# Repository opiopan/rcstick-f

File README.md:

rcstick-f
====

rcstick-f is a USB HID device which has 8 analog axis.
And this device is also a RF receiver which conplient with Futaba S-FHSS protocol.<br>
This device is designed to be used to controll RC flight simulator by Futaba RC transmitter.

One of the most simple and common way to use RC transmitter as controller of RC flight simulator is handling PPM signal exported from the trainer port on a transmitter.<br>
Some simulator software can recognize PPM signal through audio input, So in this case, you have to do is just connect cable between the trainer port on a transmitter and mic input port on a PC.<br>
Or using USB dongle that convert PPM signal to USB HID device, such as [these products](https://www.ebay.com/sch/i.html?_nkw=RC+simulator+USB+dongle+cable&_sacat=0&LH_TitleDesc=0&_osacat=0&_odkw=rc+simulator+usb+dongle), is also popular.<br>
The advantages of these PPM signal based solution are inexpencive and compatibe with many transmitter products. The most disadvantages is that the cable between  a transmitter and PC is very annoying.

On the other hand, in recent years, the products that behave wireless RF receiver and USB HID device have appeared in the world. For example, [SPEKTRUM WS1000](https://www.spektrumrc.com/Products/Default.aspx?ProdID=SPMWS1000) for DSM2/DSMX protocol or [FrSky XSR-SIM](https://www.frsky-rc.com/product/xsr-sim/) for FrSky protocol.<br>
These products are designed for a specific protocol. So comatibility is lower than the PPM signal based solution. However, users can enjoy highly convenience due to wireless connection.<br>
In addition, that is more responsive and higher precision than the PPM signale based solution since there is no unnecessary data conversion such as ADC data to PPM.

The reason why I determined to start this project is that I could'nt find a such kind of wireless device supported Futaba RC protocol. (As of the begging of 2019)<br>

## Futaba S-FHSS protocol
S-FHSS is a 2.4 GHz band based RC transceiver protocol designed by Futaba.
It is not brand new protocol, However many Futaba transmitter suport this protolol. And this protocol is well analyzed. That's why I choose S-FHSS for my own receiver imprementation.

[This commentary article](https://rfengfpv.wordpress.com/2017/01/10/futaba-s-fhss-protocol-overview/) and
[this C source code](https://github.com/DeviationTX/deviation/blob/2ce0f46fe94d80198ae94fd5a6f6a008863ec420/src/protocol/sfhss_cc2500.c)
which impremens S-FHSS transmitter are very helpful to understand the protocol.
I sincerely appreciate there effort.

## PCB Design
I designed two types of PCB artworks for rcstick-f.<br>
One is sufficiently small that QFP32 package of STM32 MCU is installed, the other one is very small that QFN32 package of MCU is installed.

Both artworks are optimized to enable hand soldering by using a soldering iron. You don't need a reflow oven or a hot air gun.<br>
All pads and parts spaceing are designed to allow contacting soldering iron. grand pad located center of QFN package is also able to be soldered through a via from back side of PCB.

January 29th, 2023: USB Type-C connector version was added. |
:-|
The design of USB Type-C version was completed in February 2022, but the production was put on hold because the Type-C plug could not be obtained due to the chip shortage from time to time.<br>Recently, the availability of this part has improved, so I was finally able to manufacture it.<br>This version is also capable of hand soldering, but this time I saved time and effort by using PCB assembly service.

March 18th, 2023: QFN28 MCU version was added. |
:-|
The situation of chip shortage has eased, and the market inventory of STM32 MCUs seems to have increased.<br>However, they seem to be carefully selecting the SKUs they produce, and I received a message from someone that STM32F042K6U* QFN32 package is not available at all.<br>So I made an artwork with STM32F042G6U* QFN28 package which is good availability.<br>Unlike the other three artworks, this is not suitable for hand soldering. Because this MCU is a QFN package that does not have a pad in the center, so it is difficult to implement with a soldering iron. I manufactured it using [JLCPCB's PCB assembly service](https://jlcpcb.com).

### Design FIles
Board Type        | Eagle design files | Gerber files |Files for [JLCPCB PCB assembly service](https://jlcpcb.com/)
------------------|:-:|:-:|:-:
QFP32 MCU version | [pcb/small](pcb/small)| [rcstick-f-gerber.zip](https://raw.githubusercontent.com/wiki/opiopan/rcstick-f/data/rcstick-f-gerber.zip)| -
QFN32 MCU version | [pcb/tiny](pcb/tiny)| [rcstick-f-tiny-gerber.zip](https://raw.githubusercontent.com/wiki/opiopan/rcstick-f/data/rcstick-f-tiny-gerber.zip)| -
QFN32 MCU and USB Type-C version|[pcb/pico](pcb/pico)|[rcstick-f-pico-gerber.zip](https://raw.githubusercontent.com/wiki/opiopan/rcstick-f/data/rcstick-f-pico-gerber.zip)|[rcstick-f-pico-pcba.zip](https://raw.githubusercontent.com/wiki/opiopan/rcstick-f/data/rcstick-f-pico-pcba.zip)
QFN28 MCU and USB Type-C version|[pcb/pico2](pcb/pico2)|[rcstick-f-pico2-gerber.zip](https://raw.githubusercontent.com/wiki/opiopan/rcstick-f/data/rcstick-f-pico2-gerber.zip)|[rcstick-f-pico2-pcba.zip](https://raw.githubusercontent.com/wiki/opiopan/rcstick-f/data/rcstick-f-pico2-pcba.zip)

***Note:***<br>
Thickness of a PCB of the USB Type-c version should be 0.8mm. This constraint depends on the implementation conditions of the Type-C plug [Molex 1054440001](https://www.molex.com/molex/products/part-detail/io_connectors/1054440001).<br>

### Schematic Diagram

### BOM List

Components | Value / Product Number | Remarks
-----------|------------------------|------------------------------
U1         | STM32F042K6T*, STM32F042K6U* or STM32F042G6U* |
U2         | TI CC2500              | 
U3         | MCP1703AT-3302E/CB     | SOT-23 LDO
J1         | MOLEX 48037-0001 or MOLEX 1054440001| USB Type-A or Type-C plug
J2         | MOLEX 53047-0410       | **OPTIONAL for debugging**<br>Firmware downloading can be proceeded by using DFU mode
X1         | 16MHz Crystal (3225)   | load capacitance: 10pF
X2         | 26MHz Crystal (3225)   | load capacitance: 9pF
LED1       | OSBL1608C1A            |
SW1        | ALPS SKRPACE010        |
C1, C2, C9 | 1uF (1005)             |
C3, C4, C10, C11, C12, C15, C16| 0.1uF (1005)           |
C5         | 4.7uF (1005)           |
C6, C7     | 15pF (1005)            | need to change value if X1's load capacitance is not 10pF
C8         | 10nF (1005)
C13, C14, C17| 220pF (1005)
C18, C19   | 12pF (1005)            | need to change value if X2's load capacitance is not 9pF
C20, C21   | 100pF (1005)           |
C22, C23   | 1pF (1005)             |
C24        | 1.8pF (1005)           |
C25        | 1.5pF (1005)           |
R1         | 10K ohm (1005)         | 
R2         | 56K ohm (1005)         |
R3         | 100 ohm (1005)         |
R4         | 5.1K ohm (1005)        | need for only USB Type-C version
L1,L2,L3   | 1.2nH (1005)           |

### Case Design
You can download [STL data](https://raw.githubusercontent.com/wiki/opiopan/rcstick-f/data/case.zip) of case for tiny version of PCB. That is desined assuming that is printed by resin printer.<br>
Note that PCB thickness should be 1.2mm if you apply this case design.

## Building Firmware
1. **Requirements**<br>
[GNU Arm Embedded Toolchain](https://developer.arm.com/open-source/gnu-toolchain/gnu-rm/downloads)
must be installed in a directory indecateed by `PATH` environment variable.

2. **Downloading Source Codes**<br>

    ```shell
    $ git clone https://github.com/opiopan/rcstick-f.git
    ```

3. **Compiling**
    ```shell
    $ cd rcstick-f/firmware
    $ make all
    ```

    **NOTE**: The LED brightness can be configured by setting the **`LED_PWM`** variable at build time (0–4095, default: 80).  
    For example `make LED_PWM=4095 all` builds the firmware with the LED set to maximum brightness.

## Downloading Firmware
You can choose two way to download firmware to rcstick-f board.<br>
One is downloading firmware via SWD by using debugger. rcstick-f exports a SWD I/F at J2 connector.<br>
The other one is downloading it via USB port in DFU mode. You can switch rcstick-f in DFU mode by inserting that to USB port with the button pressed.

### Downloading via Debugger
1. **Preparing Debugger**<br>
    Make sure that a debugger is connected with rcstick-f J2 port and debugger controlling software which behave as GDB server such as OpenOCD is running.

2. **Downloading**<br>
    You can download a firmware by making ```flash``` target with ```DEBUGSERVER``` parameter.
    If debugger controlling software is running same PC, specify ```localhost``` for ```DEBUGSERVER``` parameter.

    ```shell
    $ make DEBUGSERVER=localhost flash
    ```
### Downloading via USB
1. **Install required software**<br>
    Make sure that following software is installed.
    - [dfu-util](http://dfu-util.sourceforge.net)

2. **Switching rcstick-f in DFU mode**<br>
    Insert rcstick-f to USB port with the button (SW1) is pressed.

3. **Downloading**<br>
    You can download just by making ```dfuflash``` target.

    ```shell
    $ make dfuflash
    ```

4. **Exsiting from DFU mode**<br>
    Pull out rcstick-f from USB port, then re-insert that to USB port.

## How to use rcstick-f
0. Make sure that the settings of transmitter are appropriate as [next section](#transmitter-settings).

1. Insert rcstick-f to USB port of your PC, and make sure that 
    LED on rcstick-f flashes twice every two seconds.

2. Turn on the power of RC transmitter, and make sure that transmitter protocol is S-FHSS.<br>
    When rcstick-f detect that radio waves, LED flashing pattern is changed that flash once every one second.

3. Wait until LED will light continuously that means rcstick-f is binded with RC transmitter.

4. Now you can use your RC transmitter as a joystick on your PC.<br>
    Each channel of S-FHSS transmitter is mapped to each USB HID axis as below.

    Channel  | USB HID usage
    ---------|---------------
    CH 1     | X
    CH 2     | Y
    CH 3     | Z
    CH 4     | X rotation
    CH 5     | Y rotation
    CH 6     | Z rotation
    CH 7     | Slider
    CH 8     | Slider

## Transmitter Settings
I recommend you to register a dedicated model for rcstick-f in your transmitter. That model should be satisfy following conditions.

- **Communication Protocol (REQUIRED)**<br>
    Choose ```S-FHSS``` for communication protocol since rcstick-f can recognize only S-FHSS protocol.

- **End Point (RECOMMENDED)**<br>
    Set end point for each channl as that rx PWM output pulse width will be in range between 1009us and 2031us.<br> 
    In S-HFSS packet, each channel position is expressed as 12 bit number. And that values are equivalent of PWM pulse width output from rx in microsecond. So value of a channel which is on center position will be 1520.<br>
    rcstick-f generates values for each axis of USB HID by subtracting 1520 from value in S-HFSS packet, and clips values in range of 10 bit 2's complement number, that is  between -511 to 511.<br>
    Therefore, the most efficient setting of end point is that each channel value will be in range between 1520 - 511 and 1520 + 511.<br>

    In case of [Futaba 10J](https://www.rc.futaba.co.jp/english/propo/air/10j.html), the end point settings satisfied above condition are 124% or 125% for channels 1 to 4 and 92% or 93% for channels 5 to 8.

    rcstick-f provides a helper function to determine proper endpoint ratio. Refer the [next section](#function-to-detect-value-clipping) for the details.

- **Servo Reverse (RECOMMENDED)**<br>
    In order to prevent runaway when flight simulate is started without a connection between rcstick-f and transmitter, rcstick-f set throttle axis value correspond to channel 3 as -511 that is minimum value in range of each axis.<br>
    For Futaba transmitter, the more you raise the throttle stick, the more transmitter shorten the PWM pulse width. So to align default value the above, enable servo reversing of channel 3.

## Function to detect value clipping
As mentioned previous section, setting end point ratio as largest value within the range expressiblee by rcstick-f is important. To determine that appropriate end point ratio, rcstick-f has a mode to detect clipping value for channel. <br>
Find the appropriate end point ratio as following steps.

1. **Preparing**<br>
    To ensure that movable area of servo exactly maches end point setting, make sure following settings for each channel.

    - Trim and Sub trim: should be reset
    - Dual Rate: should be 100%
    - No mixing with other channels
    - Throttle curve and Pitch curve: should start from 0% and  end to 100%

    Then, make position of all sticks, slide levers, and switches associated with channels 1 to 8 center.<br>
    If that is impossible due to association with 2 position switch, reduce end point ratio significantry for that channel.

2. **Binding rcstick-f and transmitter**<br>
    Bind transmitter with rcstick-f according to steps described in the section ["How to use rcstick-f"](#how-to-use-rcstick-f).<br>

3. **Changing mode of rcstick-f**<br>
    Press a button on the rcstick-f in order to enable a function to detect value clipping. LED on the rcstick-f will flash three times in one second.<br>
    If LED still light continuously, a channel vallue is larger than 1520 + 511 or less than 1520 - 511 at least. Make sure that all channel settings are satisfied conditions mentiond in step 1.

4. **Determining enb point ratio**<br>
    Choose any one channel, then move the stick, the slide bar, or the switch assosiated with taht channel to the maximum position or minimum position.<br>
    If LED is still flashing, the value of cahnnel is in range and is not clipped. In this case, increase end point ratio by 1% until LED is flashing.<br>
    If LED flashing pattern is changed that it light continuously, the value of channel is out of range and is clipped. In this case, decrease end point ratio by 1% by LED start to flash.<br>

    Usually, you can apply same ratio determined above for all other channels. However you should be careful if your transmitter is entry model such as [10J](https://www.rc.futaba.co.jp/english/propo/air/10j.html).<br>
    It's well known taht servo angle in 100% end point for channels 5 and later is wider than the servo angle for channels 1 to 4 in some Futaba transmitter. If you use that kind of transmitter, you need to determine for two channels at least.

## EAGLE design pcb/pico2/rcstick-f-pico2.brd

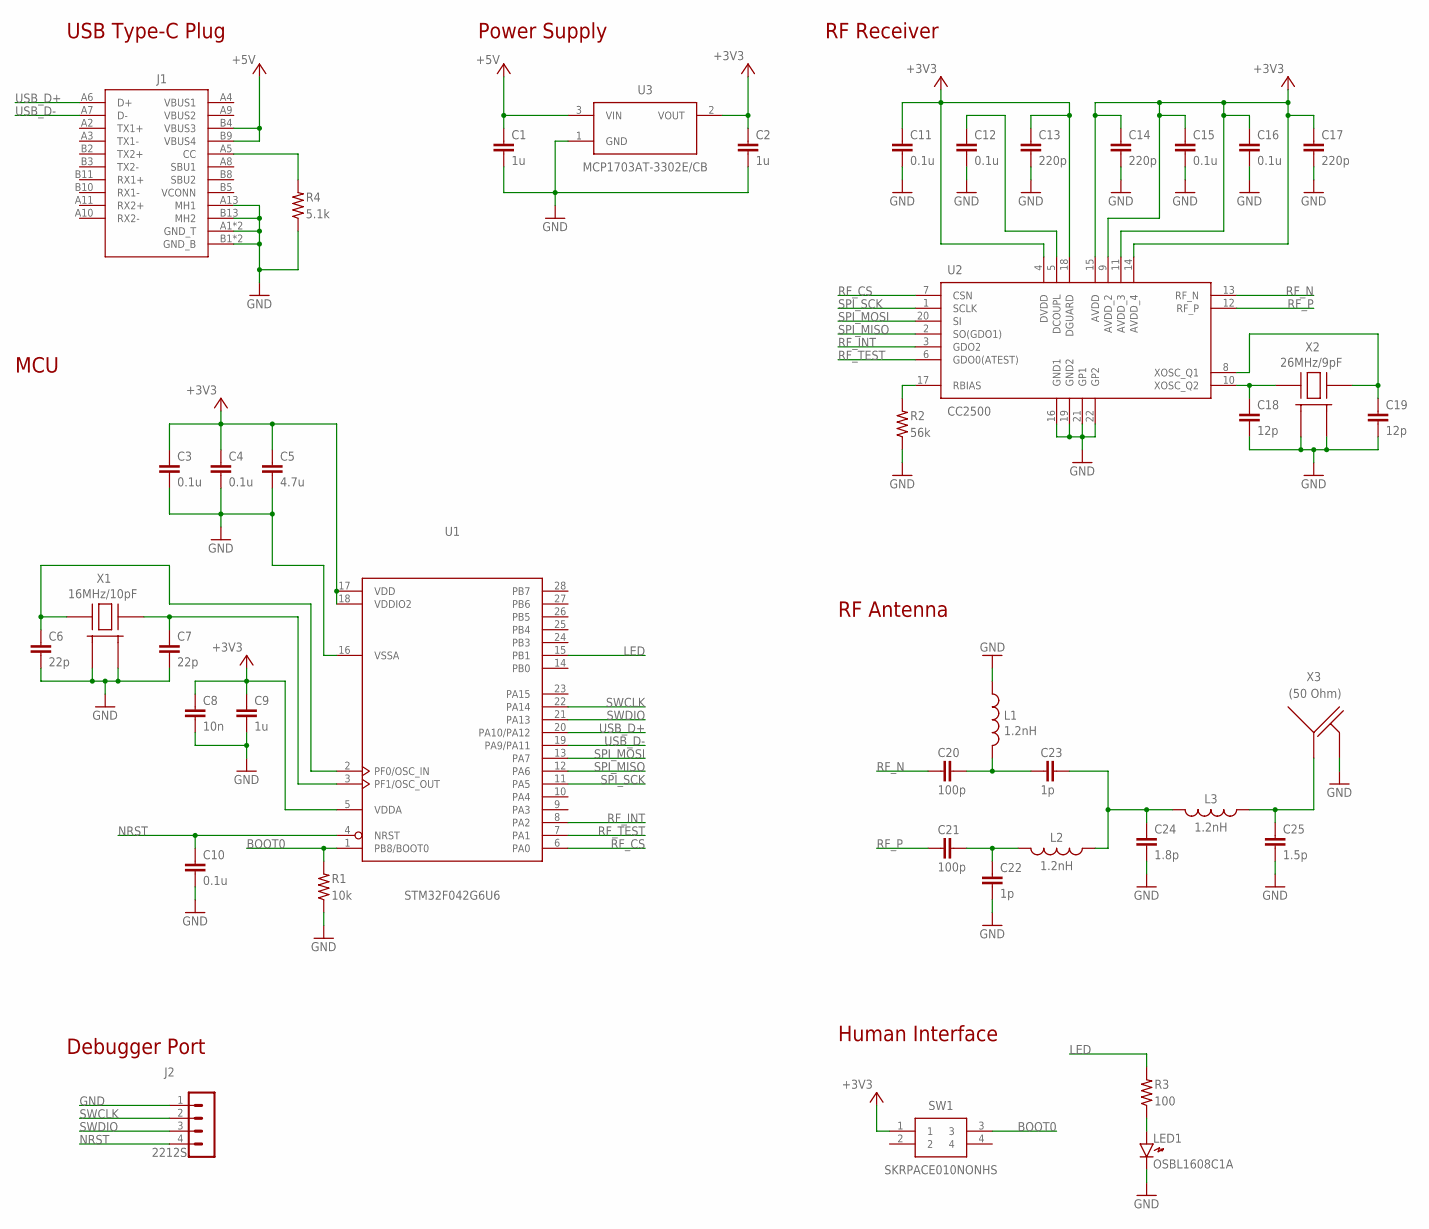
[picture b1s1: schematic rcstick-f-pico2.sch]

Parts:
C1, C2, C9: 1u; RCL_C0402_HS
C3, C4, C10, C11, C12, C15, C16: 0.1u; RCL_C0402_HS
C5: 4.7u; RCL_C0402_HS
C6, C7: 22p; RCL_C0402_HS
C8: 10n; RCL_C0402_HS
C13, C14, C17: 220p; RCL_C0402_HS
C18, C19: 12p; RCL_C0402_HS
C20, C21: 100p; RCL_C0402_HS
C22, C23: 1p; RCL_C0402_HS
C24: 1.8p; RCL_C0402_HS
C25: 1.5p; RCL_C0402_HS
J1: USB-TYPEC-1054440001-HS
J2: 2212S; 53047-0410
L1, L2, L3: 1.2nH; RCL_L0402_HS
LED1: OSBL1608C1A; LED1608NONHS
R1: 10k; RCL_R0402_HS
R2: 56k; RCL_R0402_HS
R3: 100; RCL_R0402_HS
R4: 5.1k; RCL_R0402_HS
SW1: SKRPACE010NONHS; SMT(4.2X3.2)_ORG
U1: STM32F042G6U6; UFQFPN28
U2: CC2500; CC2500-RTY1_CC2500
U3: MCP1703AT-3302E/CB; SOT23_NOHS
X1: 16MHz/10pF; CRYSTAL3225
X2: 26MHz/9pF; CRYSTAL3225
X3: (50 Ohm); 2.4GHZ-INVERTED-F-SMALL-FLIP

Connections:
+3V3: C2.1, C3.1, C4.1, C5.1, C8.1, C9.1, C11.1, C13.1, C14.1, C15.1, C16.1, C17.1, SW1.1, U1.5 (VDDA), U1.17 (VDD), U1.18 (VDDIO2), U2.4 (DVDD), U2.9 (AVDD_2), U2.11 (AVDD_3), U2.14 (AVDD_4), U2.15 (AVDD), U2.18 (DGUARD), U3.2 (VOUT)
+5V: C1.1, J1.B4 (VBUS3), J1.B9 (VBUS4), U3.3 (VIN)
BOOT0: R1.2, SW1.3, U1.1 (PB8/BOOT0)
CC: J1.A5 (CC), R4.2
DCOUPL: C12.1, U2.5 (DCOUPL)
GND: C1.2, C2.2, C3.2, C4.2, C5.2, C6.2, C7.2, C8.2, C9.2, C10.2, C11.2, C12.2, C13.2, C14.2, C15.2, C16.2, C17.2, C18.2, C19.2, C22.2, C24.2, C25.2, J1.A1 (GND_T), J1.A12 (GND_T), J1.A13 (MH1), J1.B1 (GND_B), J1.B12 (GND_B), J1.B13 (MH2), J2.1, L1.1, LED1.K, R1.1, R2.1, R4.1, U1.16 (VSSA), U2.16 (GND1), U2.19 (GND2), U2.21 (GP1), U2.22 (GP2), U3.1 (GND), X1.2 (GND_1), X1.4 (GND_2), X2.2 (GND_1), X2.4 (GND_2), X3.2 (GND)
LED: R3.2, U1.15 (PB1)
unnamed: LED1.A, R3.1
unnamed: C20.2, C23.1, L1.2
unnamed: C21.2, C22.1, L2.2
unnamed: C23.2, C24.1, L2.1, L3.2
unnamed: C25.1, L3.1, X3.1 (ANT)
NRST: C10.1, J2.4, U1.4 (NRST)
OSC_IN: C6.1, U1.2 (PF0/OSC_IN), X1.1 (HOT_1)
OSC_OUT: C7.1, U1.3 (PF1/OSC_OUT), X1.3 (HOT_2)
RBIAS: R2.2, U2.17 (RBIAS)
RF_CS: U1.6 (PA0), U2.7 (CSN)
RF_INT: U1.8 (PA2), U2.3 (GDO2)
RF_N: C20.1, U2.13 (RF_N)
RF_P: C21.1, U2.12 (RF_P)
RF_TEST: U1.7 (PA1), U2.6 (GDO0(ATEST))
SPI_MISO: U1.12 (PA6), U2.2 (SO(GDO1))
SPI_MOSI: U1.13 (PA7), U2.20 (SI)
SPI_SCK: U1.11 (PA5), U2.1 (SCLK)
SWCLK: J2.2, U1.22 (PA14)
SWDIO: J2.3, U1.21 (PA13)
USB_D+: J1.A6 (D+), U1.20 (PA10/PA12)
USB_D-: J1.A7 (D-), U1.19 (PA9/PA11)
XOSC1: C19.1, U2.8 (XOSC_Q1), X2.3 (HOT_2)
XOSC2: C18.1, U2.10 (XOSC_Q2), X2.1 (HOT_1)

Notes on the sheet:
USB Type-C Plug
Power Supply
MCU
RF Receiver
RF Antenna
Human Interface
Debugger Port

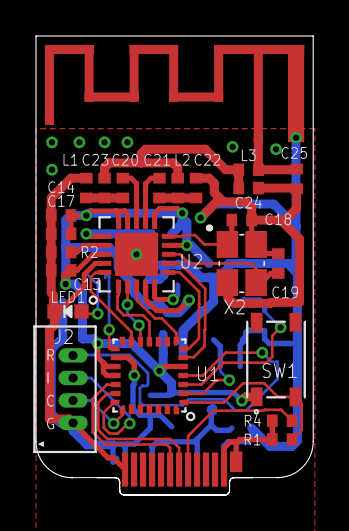
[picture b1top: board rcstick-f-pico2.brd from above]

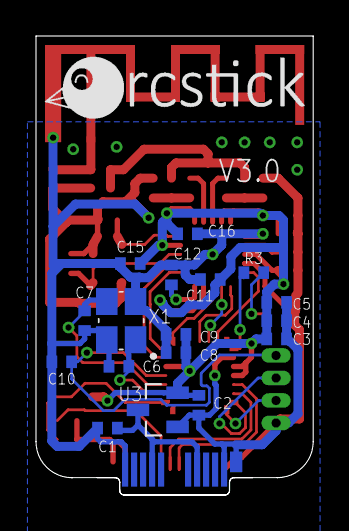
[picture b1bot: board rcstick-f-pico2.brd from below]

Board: 2 copper layers, 15.4 x 25.5 mm, 43 parts (18 on the bottom side), 30 nets.

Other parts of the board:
U$1: RCSTICK-LOGO

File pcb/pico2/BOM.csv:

Comment,Designator,Footprint,LCSC Part # (optional)
STM32F042G6U6,"U1",UFQFPN-28_L4.0-W4.0-P0.50-BL,C961597
CC2500,"U2",QFN-20_L4.0-W4.0-P0.50-TL-EP2.7,C57494
MCP1703AT-3302E/CB,"U3",SOT-23-3_L2.9-W1.3-P1.90-LS2.4-BR,C144183
16MHZ_9pF,"X1",OSC-SMD_4P-L3.2-W2.5-BL,C13738
26MHZ_8pF,"X2",OSC-SMD_4P-L3.2-W2.5-BL,C156251
BLUE-LED,"LED1",LED-SMD_L1.6-W0.8-R-RD,C375446
SKRPACE010,"SW1",KEY-SMD_4P-L4.2-W3.2-P2.20-LS4.6,C139797
1uF,"C1,C2,C9",C0402,C52923
100nF,"C3,C4,C10,C11,C12,C15,C16",C0402,C1525
4.7uF,"C5",C0402,C23733
13pF,"C6,C7",C0402,C326790
10nF,"C8",C0402,C15195
220pF,"C13, C14, C17",C0402,C1530
11pF,"C18, C19",C0402,C527000
100pF,"C20, C21",C0402,C343043
1pF,"C22, C23",C0402,C147337
1.8pF,"C24",C0402,C301970
1.5pF,"C25",C0402,C338137
10KOHMS,"R1",R0402,C25744
56KOHMS,"R2",R0402,C173699
27.4OHMS,"R3",R0402,C274349
5.1KOHMS,"R4",R0402,C25905
1.2nH,"L1,L2,L3",L0402,C162537
1054440001,"J1",,C134082

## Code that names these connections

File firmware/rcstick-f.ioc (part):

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Mcu.Name=STM32F042K(4-6)Tx
Mcu.Package=LQFP32
Mcu.UserName=STM32F042K6Tx
PA0.GPIOParameters=PinState,GPIO_Label
PA0.GPIO_Label=RF_CS
PA0.PinState=GPIO_PIN_SET
PA0.Signal=GPIO_Output
PA1.GPIOParameters=GPIO_Label
PA1.GPIO_Label=RF_TEST
PA1.Signal=GPIO_Input
PA11.Mode=Device
PA11.Signal=USB_DM
PA12.Mode=Device
PA12.Signal=USB_DP
PA13.Mode=Serial_Wire
PA13.Signal=SYS_SWDIO
PA14.Mode=Serial_Wire
PA14.Signal=SYS_SWCLK
PA2.GPIOParameters=GPIO_Label
PA2.GPIO_Label=RF_INT
PA2.Signal=GPXTI2
PA5.Mode=Full_Duplex_Master
PA5.Signal=SPI1_SCK
PA6.Mode=Full_Duplex_Master
PA6.Signal=SPI1_MISO
PA7.Mode=Full_Duplex_Master
PA7.Signal=SPI1_MOSI
PB1.GPIOParameters=GPIO_Label
PB1.GPIO_Label=LED
PB1.Signal=S_TIM3_CH4
PB8.GPIOParameters=GPIO_Label,GPIO_ModeDefaultEXTI
PB8.GPIO_Label=BUTTON
PB8.GPIO_ModeDefaultEXTI=GPIO_MODE_IT_RISING_FALLING
PB8.Signal=GPXTI8
PF0-OSC_IN.Mode=HSE-External-Oscillator
PF0-OSC_IN.Signal=RCC_OSC_IN
PF1-OSC_OUT.Mode=HSE-External-Oscillator
PF1-OSC_OUT.Signal=RCC_OSC_OUT
RCC.HSE_VALUE=16000000
RCC.SYSCLKFreq_VALUE=48000000
RCC.SYSCLKSource=RCC_SYSCLKSOURCE_PLLCLK
board=custom

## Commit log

2019-02-21 add README
2019-02-23 renumbering capacities
2019-02-23 refine wiring
2019-03-04 minor update
2019-03-31 add panelizing script
2019-04-09 update status
2019-04-13 add firmaware code base
2019-05-04 add LED and button control capability
2019-05-04 improve logging
2019-05-05 improve error handling
2019-05-06 fix many bugs using bread board based mock up
2019-12-19 add script to support making 3d model
2020-05-24 added new formfactor artwork for QFN32 package of STM32 MCU
2020-05-26 change art work of tiny board
2020-07-13 improve connection stability
2020-07-18 update logging
2020-07-19 each axis resolution in USB HID expands to 12 bit from 8 bit
2020-07-19 minor refactoring
2020-07-19 fix minor issue
2020-07-20 fix a HID long latency issue
2020-07-24 change HID report descriptor due to support CH 7 and CH 8
2020-07-26 change HID usage for 8-CH in order to work on Mac
2020-08-01 optimize range of value for each HID axis and add a function to find value clipping
2020-08-02 improve durability of connection
2020-08-03 change RF analog artwork for tiny version
2020-08-15 add case 3D data
2020-08-16 modify README
2020-08-29 improve SPI transfer efficiency between SMT32 and CC2500
2020-08-30 refactoring around S-FHSS protocol process
2020-08-30 improve SPI transfer efficiency and CPU utilization by using DMA
2020-08-30 refactoring
2020-09-03 refactoring and add experimental code
2020-09-20 add experimental code working at once on boot
2020-09-21 generating firmware version string automatically
2020-11-02 fix minor issue of tiny artwork
2021-10-27 Update readme.md
    please work.
2023-01-29 added USB Type-C version
2023-03-18 added QFN28 MCU version
2023-03-19 now firmware supports STM32F042G6U*
2024-10-05 The footprint for a Type-C connector has been registered with JLCPCB, but since the origin and angle differ from my library, I made fine adjustments using a script to generate the CPL file.
2026-01-24 allowed configuring LED brightness via a make variable
